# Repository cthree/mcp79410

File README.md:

# RTCC - MCP79410 Breakout Board

A small breakout board for the MCP79410 I2C RTCC/EEPROM and UID chip from Microchip.

You can [order this board](https://oshpark.com/shared_projects/WmGSs4wK) ready made
from oshpark.com. It's 1" x 1" so it will cost $5 for 3.

I use these to prototype new projects needing an RTCC. Feel free to do the same.
I designed this to be easy to hand solder. The battery holder and battery are
optional, you can use the VBAT pin as an alternate. VBAT can be used as a
battery level fuel gauge sense line if you connect it to an ADC.

R2 and R3 are 2K2 I2C pullup resistors which you may not need if you've got
pullups configured on your microcontroller ports or if you have them on your
bus already. Consider them optional.

The passives are all 0603 ERJ-3GEYJxxx Panasonic resistors and GRM188xxxxxx
capacitors from muRata. See the BOM for a complete parts list. Everything is
available from Digikey, this [saved cart](http://www.digikey.ca/short/3wd48v)
has everything you'll need.

Total cost for 3 PCBs and the parts to build them out works out to about $14.

When mounting and handling the module be aware that the battery holder is at +3V.
Don't accidentally short it to ground or you can expect undesired results. The
mounting holes close to the pins are unplated to avoid accidentally shorting to
ground with a screw head. Take care and maybe put some electrical tape over the
battery holder just in case.

## About the MCP794XX Realtime Clock/Calendar

The [Datasheet](http://ww1.microchip.com/downloads/en/DeviceDoc/20002266H.pdf)
is your primary reference. In addition there are a few
[Application Notes](http://www.microchip.com/wwwproducts/en/mcp79410)

The MCP7941x is a mid-range real-time clocks with advanced timekeeping features
such as the Power-Fail Timestamp, which can be used to log the time and duration
of power failures. With onboard digital trimming, these devices can provide
accurate timekeeping over a wide temperature range.

* 400 KHz I2C bus
* Battery Switchover (VBAT)
* Power-Fail Timestamp
* Digital trimming = +/- 127 PPM
* Compensates up to ~11 sec/day
* SRAM = 64 bytes
* EEPROM = 1K or 0K bits
* Unique ID = 64 bits

The 79410, 79411 and 79412 are all compatible with this breakout. The difference
between them is what is stored in the the 64 bit UID at the factory:

* MCP79410: Blank
* MCP79411: EUI-48
* MCP79412: EUI-64

Check the datasheet for details. The MCP79410 spec'ed for this breakout has
1Kbits of EEPROM and a blank UID.

## Software

### Linux

The MCP7941X is compatible with the DS-1307 RTCC. It is located at I2C address
0x6e. You'll want to use the rtc-ds1307 kernel driver available from kernel v3.19
on.

### Arduino/AVR

[Arduino MCP79412 RTC Library v1.0](https://github.com/JChristensen/MCP79412RTC)

###PIC

[AN1355](http://www.microchip.com//wwwAppNotes/AppNotes.aspx?appnote=en551346)
[AN1355 Code](http://ww1.microchip.com/downloads/en/DeviceDoc/RTCC_I2C_MCSET_FJ11_B06.zip)

### MSP430

[Driver](https://github.com/sbobovyc/MSP430/blob/master/I2C_test/RTCC_Driver.c)

## Bugs, Issues and Contributions

If you discover any issues with it or the parts used please let me know by opening
an issue or forking the repo and submitting a pull request with your fix.

Happy hacking!

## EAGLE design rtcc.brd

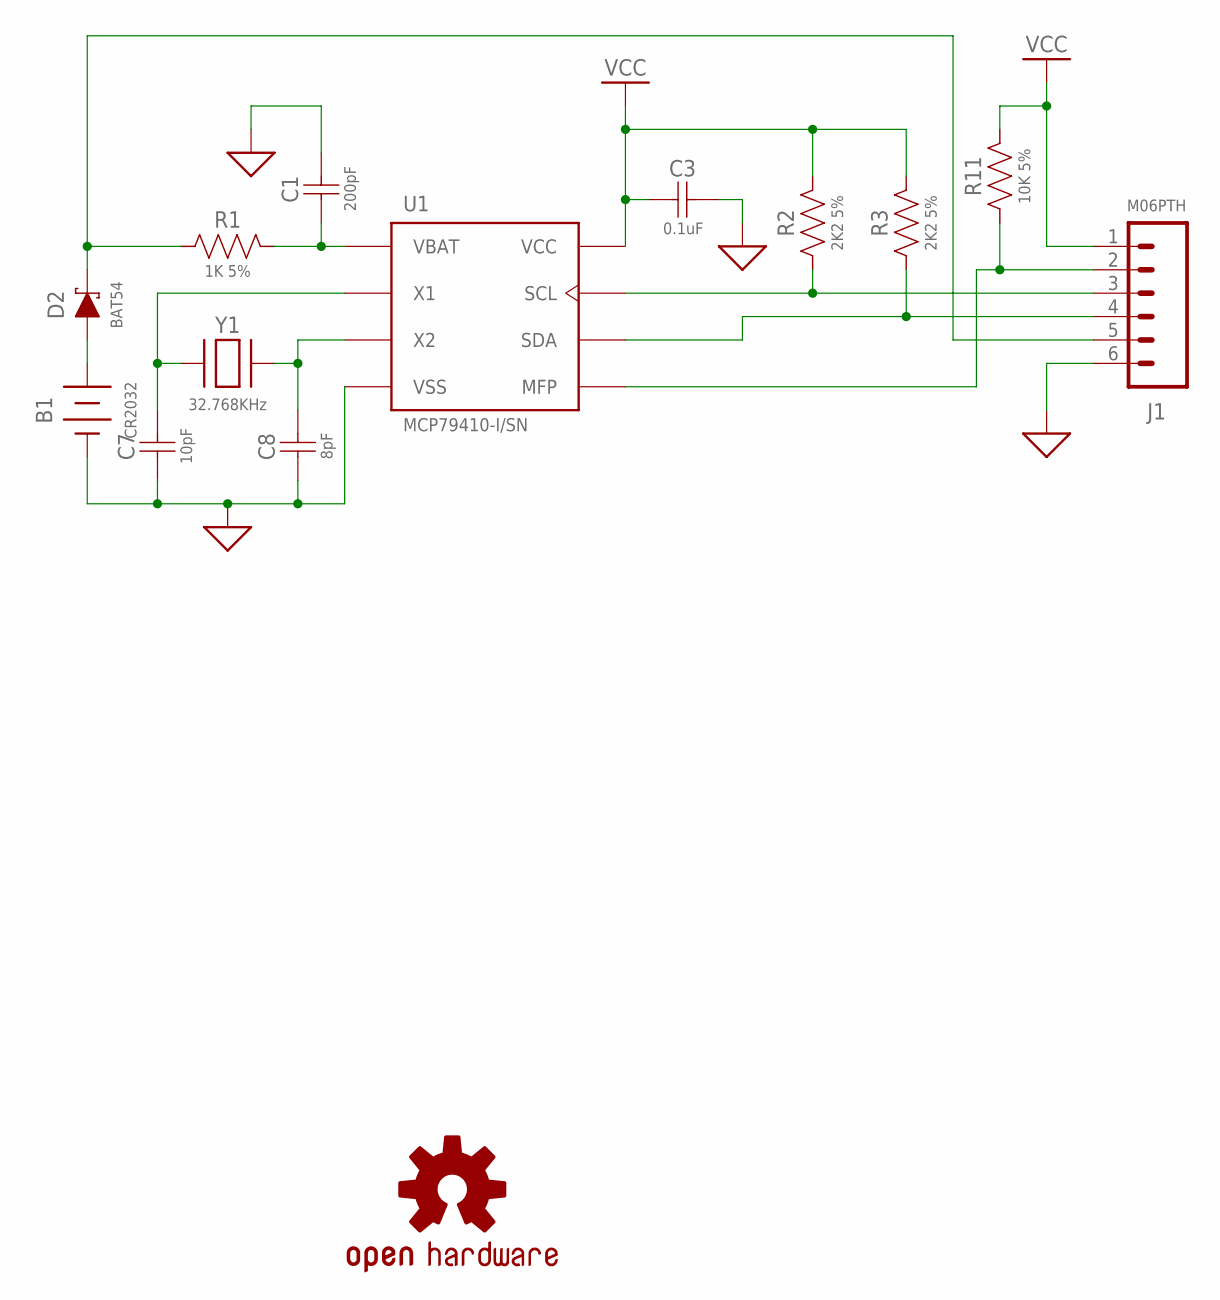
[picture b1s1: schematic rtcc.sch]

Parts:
B1: CR2032; BK-912
C1: 200pF; 18-0603
C3: 0.1uF; 18-0603
C7: 10pF; 18-0603_NOSILK
C8: 8pF; 18-0603_NOSILK
D2: BAT54; SOT23-3
J1: M06PTH; 1X06
LOGO1: OSHW-LOGOS; OSHW-LOGO-S
R1: 1K 5%; R0603
R2, R3: 2K2 5%; R0603
R11: 10K 5%; R0603
U1: MCP79410-I/SN; SOIC8-N_MC
Y1: 32.768KHz; 4-SOJ

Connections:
BSENSE: D2.C, J1.5, R1.1
GND: B1.NEG (GND), C1.2, C3.2, C7.1, C8.1, J1.6, U1.4 (VSS)
RTCMFP: J1.2, R11.1, U1.7 (MFP)
SCL: J1.3, R2.1, U1.6 (SCL)
SDA: J1.4, R3.1, U1.5 (SDA)
VBAT: B1.POS1 (VBAT), B1.POS2 (VBAT), D2.A
VBAT_IN: C1.1, R1.2, U1.3 (VBAT)
VCC: C3.1, J1.1, R2.2, R3.2, R11.2, U1.8 (VCC)
Y1: C7.2, U1.1 (X1), Y1.1 (A)
Y2: C8.2, U1.2 (X2), Y1.4 (B)

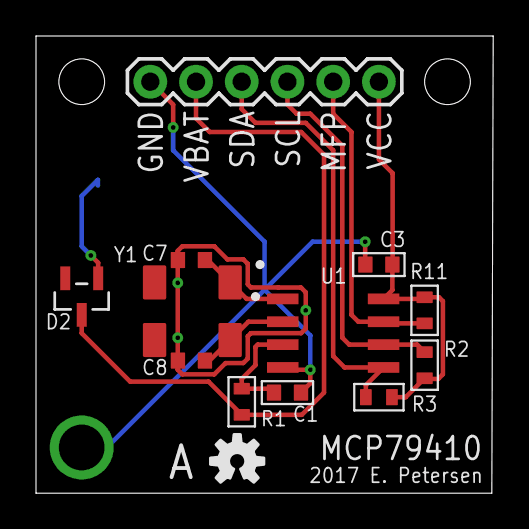
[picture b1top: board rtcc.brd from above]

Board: 2 copper layers, 25.4 x 25.4 mm, 14 parts (1 on the bottom side), 10 nets.

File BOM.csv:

"Part","Value","Device","Package","Description"
"B1","CR2032","BK-912","BK-912","MPD BK-912 SMD 20mm Coin Cell Battery Holder"
"C1","200pF","GRM1885C1H201JA01","0603","Murata SMD Ceramic Capacitor"
"C3","0.1uF","GRM188R71E104KA01","0603","Murata SMD Ceramic Capacitor"
"C7","10pF","GRM1885C1H100JA01NS","0603","Murata SMD Ceramic Capacitor"
"C8","8pF","GRM1885C1H8R0DZ01NS","0603","Murata SMD Ceramic Capacitor"
"D2","BAT54","BAT54","SOT23","FAIRCHILD SINGLE SCHOTTKY DIODE"
"J1","M06PTH","M06PTH","1X06","0.100in Male Header 1x6"
"R1","1K 5%","ERJ-3GEYJ102","0603","Panasonic ERJ Thick Film Chip Resistor"
"R2","2K2 5%","ERJ-3GEYJ222","0603","Panasonic ERJ Thick Film Chip Resistor"
"R3","2K2 5%","ERJ-3GEYJ222","0603","Panasonic ERJ Thick Film Chip Resistor"
"R11","10K 5%","ERJ-3GEYJ103","0603","Panasonic ERJ Thick Film Chip Resistor"
"U1","MCP79410-I/SN","MCP79410-I/SN","SOIC8-N_MC","MCP79XXX RTCC Real Time Clock Calendar - I2C Bus"
"Y1","32.768KHz","CM200C32768DZBT","4-SOJ","Citizen CM Series 32.768KHz Tuning Fork Crystal - 6pF"

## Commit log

2017-04-17 Added images to README
2017-04-17 Filled out the README
